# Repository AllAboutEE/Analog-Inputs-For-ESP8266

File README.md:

# MCP3021 Array Breakout Board
A breakout board for four (4) I2C 10-bit analog to digital (A/D) converters. 

#### What is it?
A board with four analog to digital (A/D) converters that your ESP8266 can interface with it using I2C.

#### Why did you make it?
The ESP8266 is great module, but it lacks some functionality that it's often necessary to use another microcontroller to accomplish what you want. One of the features that it lacks are A/D converters (it only has one and it's hard to access if you have the ESP-01 version).

#### Technical Details

- 4 Microchip MCP3021 A/D converters
- I2C interface
- 10-bit resolution
- Single supply specified operation: 2.7V to 5.5V

[MCP3021 A/D converter datasheet](http://ww1.microchip.com/downloads/en/DeviceDoc/21805B.pdf)

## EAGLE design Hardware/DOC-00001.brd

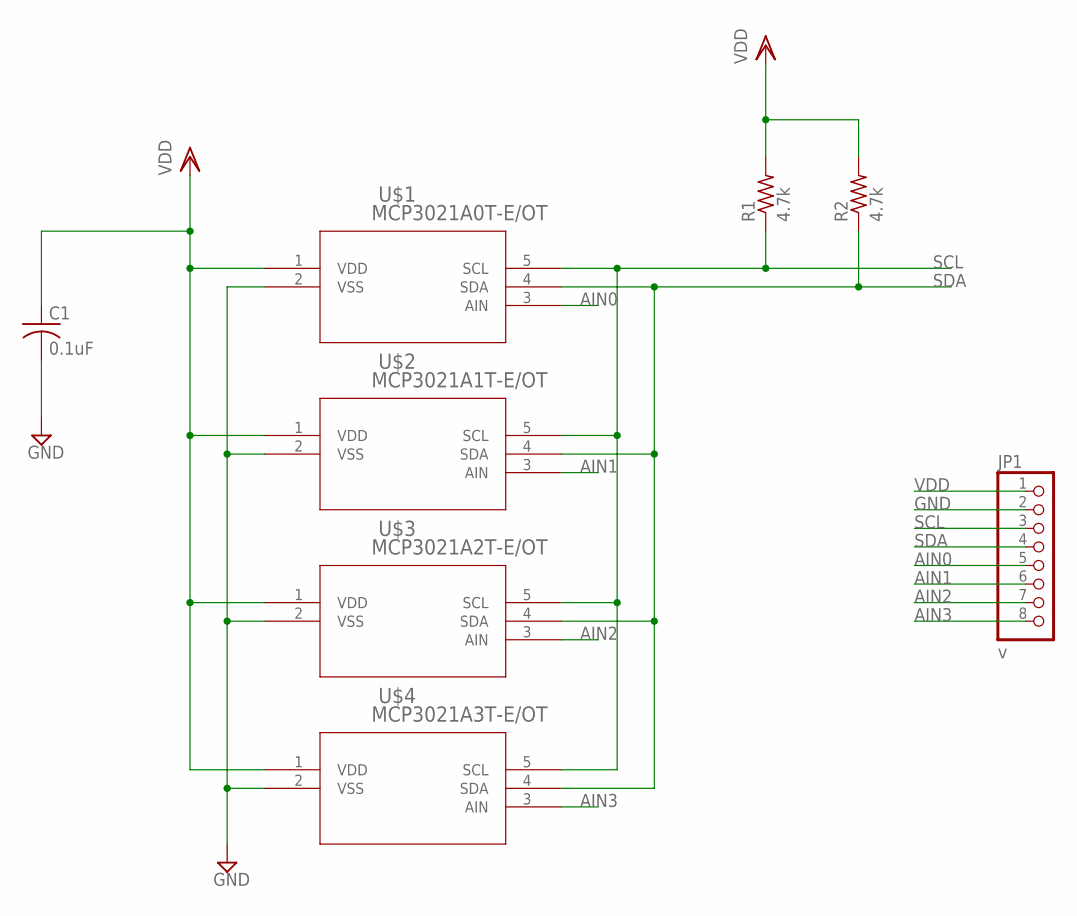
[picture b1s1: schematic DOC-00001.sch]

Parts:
C1: 0.1uF; C0805K; MPN VJ0805Y104MXXAC
JP1: v; 1X08; MPN 825433-8
R1, R2: 4.7k; R0805; MPN CRCW08054K70FKEA
U$1: MCP3021A0T-E/OT; SOT-23-5_MC; MPN MCP3021A0T-E/OT
U$2: MCP3021A1T-E/OT; SOT-23-5_MC; MPN MCP3021A1T-E/OT
U$3: MCP3021A2T-E/OT; SOT-23-5_MC; MPN MCP3021A2T-E/OT
U$4: MCP3021A3T-E/OT; SOT-23-5_MC; MPN MCP3021A3T-E/OT

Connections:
AIN0: JP1.5, U$1.3 (AIN)
AIN1: JP1.6, U$2.3 (AIN)
AIN2: JP1.7, U$3.3 (AIN)
AIN3: JP1.8, U$4.3 (AIN)
GND: C1.2, JP1.2, U$1.2 (VSS), U$2.2 (VSS), U$3.2 (VSS), U$4.2 (VSS)
SCL: JP1.3, R1.1, U$1.5 (SCL), U$2.5 (SCL), U$3.5 (SCL), U$4.5 (SCL)
SDA: JP1.4, R2.1, U$1.4 (SDA), U$2.4 (SDA), U$3.4 (SDA), U$4.4 (SDA)
VDD: C1.1, JP1.1, R1.2, R2.2, U$1.1 (VDD), U$2.1 (VDD), U$3.1 (VDD), U$4.1 (VDD)

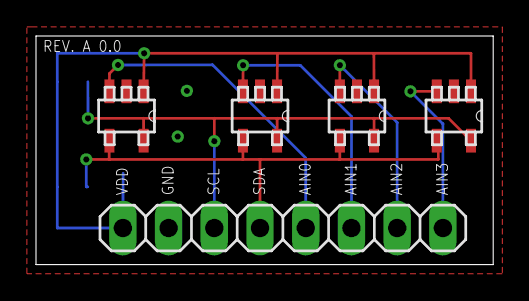
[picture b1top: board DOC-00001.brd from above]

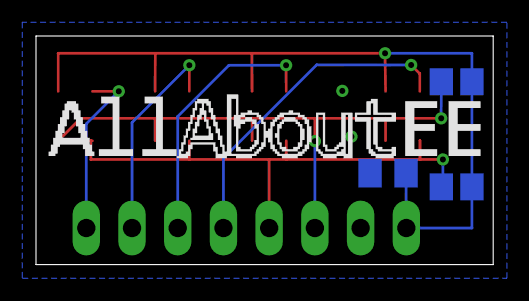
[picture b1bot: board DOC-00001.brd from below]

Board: 2 copper layers, 25.4 x 12.7 mm, 8 parts (3 on the bottom side), 8 nets.

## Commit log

2015-03-19 First commit. Added schematic and board files.
2015-03-19 Routed. Needs ground layers.
2015-03-19 Added BOM.
2015-03-19 Added HTML extension to BOM.
2015-03-19 Added txt version of BOM.
2015-03-19 Changed the PCB layout
2015-03-20 Fixed values of Ux in sch to match PCBs, there was a space after the value name so I just deleted that. Added cost sheet.
2015-04-12 Added header and cpp file template.
2015-04-13 Working Libraries and single read example
2015-04-13 Fixed I2C address in library and added for loop
2015-04-13 Documented and described functions.
2015-04-13 Removed SlickEdit project files from repo.
2015-04-13 Renamed examples to have a better looking name.
2015-04-13 Commented examples to explain what they do.
2015-04-18 Completed version. This was uploaded to OSHPARK
2015-04-18 Deleted brd and sch because merging was a mess so I'll just put the files that were uploaded to OSH park in the next commit.
2015-04-18 Re added files that were deleted.
2015-04-18 Added Arduino library.
2015-04-18 Renamed arduino library folder.
2015-04-18 Added NodeMcu library Renamed Arduino library
